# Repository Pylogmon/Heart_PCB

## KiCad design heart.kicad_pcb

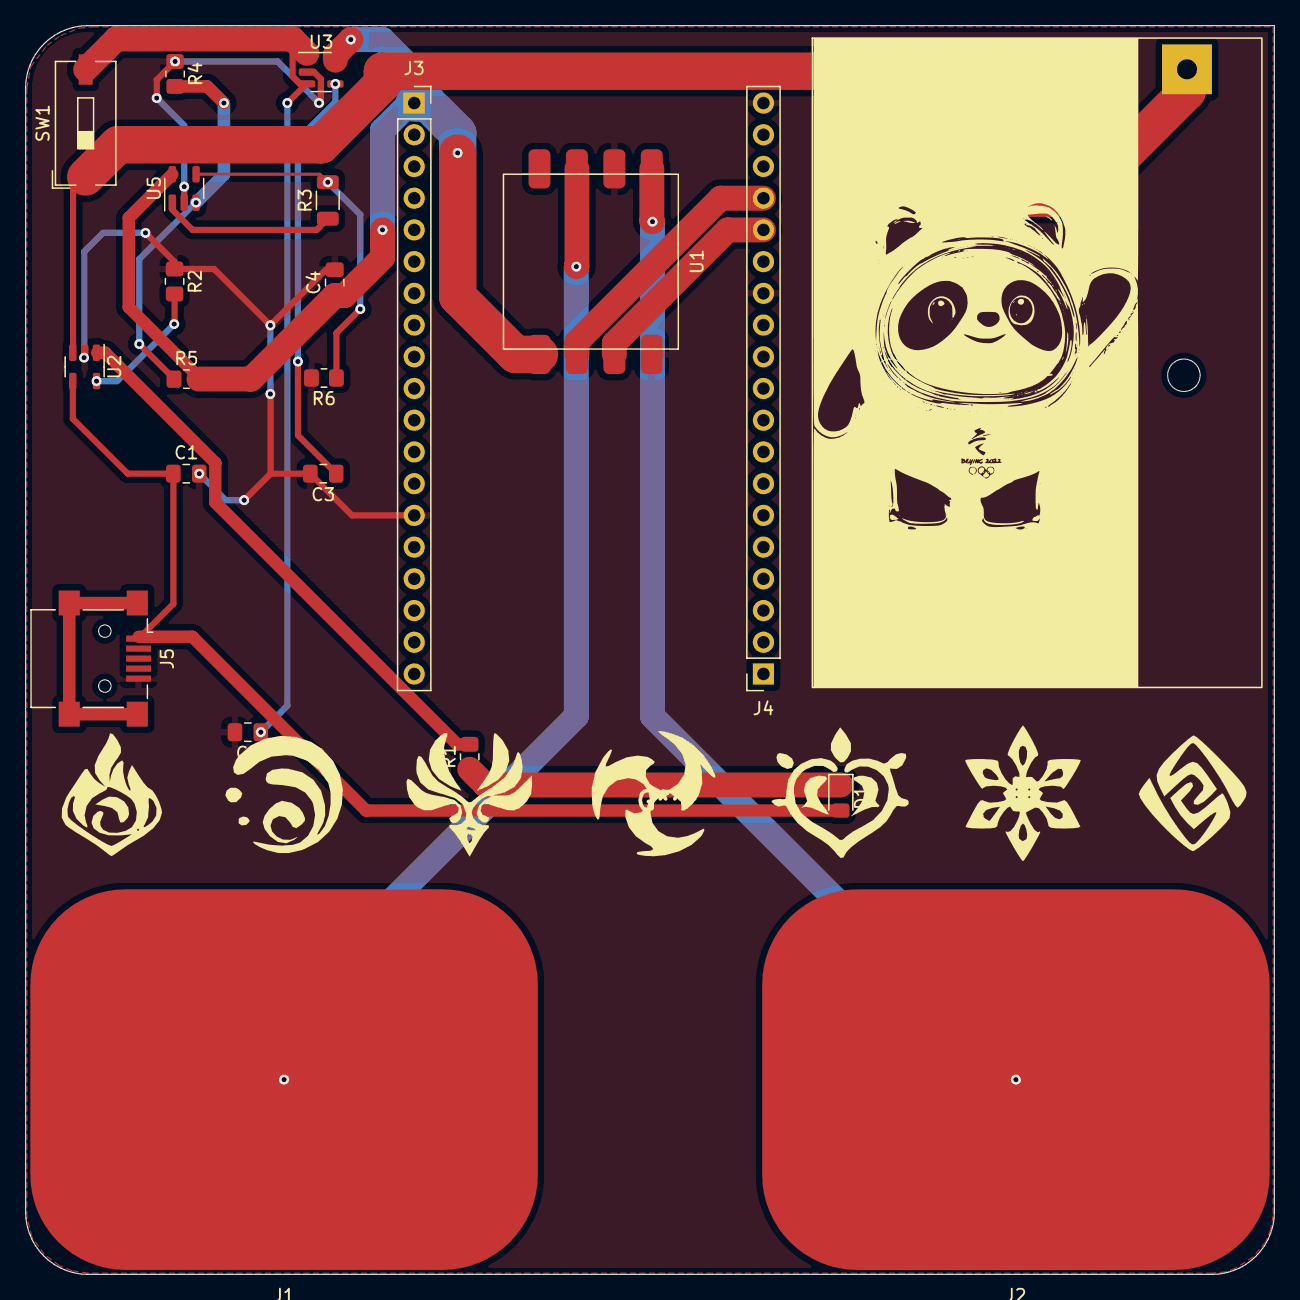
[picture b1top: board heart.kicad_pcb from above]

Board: 2 copper layers, 100.0 x 100.0 mm, 22 parts (0 on the bottom side), 16 nets.

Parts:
BT1: Battery_Cell; battary
C1: 0.1μF; C_0805_2012Metric_Pad1.18x1.45mm_HandSolder
C2, C4: 1μF; C_0805_2012Metric_Pad1.18x1.45mm_HandSolder
C3: 0.01μF; C_0805_2012Metric_Pad1.18x1.45mm_HandSolder
D1: LED; LED_0805_2012Metric_Pad1.15x1.40mm_HandSolder
J1: Positive; Square_Pad_40mm*30mm
J2: Negative; Square_Pad_40mm*30mm
J3, J4: Conn_01x19_Female; PinSocket_1x19_P2.54mm_Vertical
J5: USB_B_Mini; USB_Mini-B_Lumberg_2486_01_Horizontal
R1, R2: 1K; R_0805_2012Metric_Pad1.20x1.40mm_HandSolder
R3: MF52; R_1206_3216Metric
R4, R6: 10 k; R_0805_2012Metric_Pad1.20x1.40mm_HandSolder
R5: 30 k; R_0805_2012Metric_Pad1.20x1.40mm_HandSolder
SW1: SW_DIP_x01; SW_DIP_SPSTx01_Slide_9.78x4.72mm_W8.61mm_P2.54mm
U1: BMD101
U2: TP4054; SOT-23-5
U3: RS3236; SOT-23-5
U5: RS8051; SOT-23-5

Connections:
/BT+: BT1.1 (+), SW1.1, U2.3 (BAT)
/RX: J4.15 (RX), U1.3 (TX)
/TX: J4.16 (TX), U1.2 (RX)
/VCC: C4.1, J3.1 (3.3V), R5.2, U1.1 (VCC), U3.5 (OUT), U5.5 (V+)
GNDREF: BT1.2 (-), C1.2, C2.2, C3.2, C4.2, J3.14 (GND), J4.13 (GND), J4.19 (GND), J5.5 (GND), R2.1, R4.1, R6.2, U1.4 (GND), U1.6 (O), U2.2 (GND), U3.2 (GND), U5.2 (V-)
unnamed: C1.1, D1.2 (A), J5.1 (VBUS), U2.4 (VCC)
unnamed: C2.1, SW1.2, U3.1 (IN), U3.3 (EN)
unnamed: C3.1, U3.4 (BP)
unnamed: D1.1 (K), R1.1
unnamed: J1.1, U1.7
unnamed: J2.1, U1.5 (N)
unnamed: R1.2, U2.1 (GHRG_L)
unnamed: R2.2, U2.5 (PROG)
unnamed: R3.1, U5.1 (OUT)
unnamed: R3.2, R6.1, U5.4 (-IN)
unnamed: R4.2, R5.1, U5.3 (+IN)

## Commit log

2022-03-22 backup
2022-04-07 最终投板
